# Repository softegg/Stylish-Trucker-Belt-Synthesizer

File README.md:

# Stylish-Trucker-Belt-Synthesizer
A stylus-based music synthesizer you can wear as a belt! 

Conceived as a piece of premium swag for the MAGwest convention, "Stylish!" investigates how cheaply one can make a real, useful monophonic, digital (virtual analog) music synthesizer! Borrowing the stylus-based keyboard from the venerable Stylophone, and adding complete synthesis features like multiple oscillators, filters, envelopes, vibrato, etc. that are fully adjustable so that you can make your own sounds! It may even end up with a step sequencer and drum loop! 
Let's bring real music synthesis to the masses, stylishly!

Project is based around the "Blue Pill" STM32F103C8T6 microcontroller board that can be obtained from AliExpress for less than $2.

Code is written using Arduino IDE and STM32Duino.

Audio output is via PWM (10k resistor + 1uF capacitor) using the Mozzi library. CC4.0 Share Alike Non-commercial license applies.

LEDs are WS2812B, and the project PCB includes a header to use a standard 16 LED ring.

Amplifier is XH-M125 based on the XPT8871, which you an also buy cheaply from AliExpress. Headers are included to simply mount this board on the unit if you don't want to solder all of those parts.

Speaker is 40-50mm 0.5W 8 Ohm

<br />This work is licensed under a <a rel="license" href="http://creativecommons.org/licenses/by-nc-sa/4.0/">Creative Commons Attribution-NonCommercial-ShareAlike 4.0 International License</a>.

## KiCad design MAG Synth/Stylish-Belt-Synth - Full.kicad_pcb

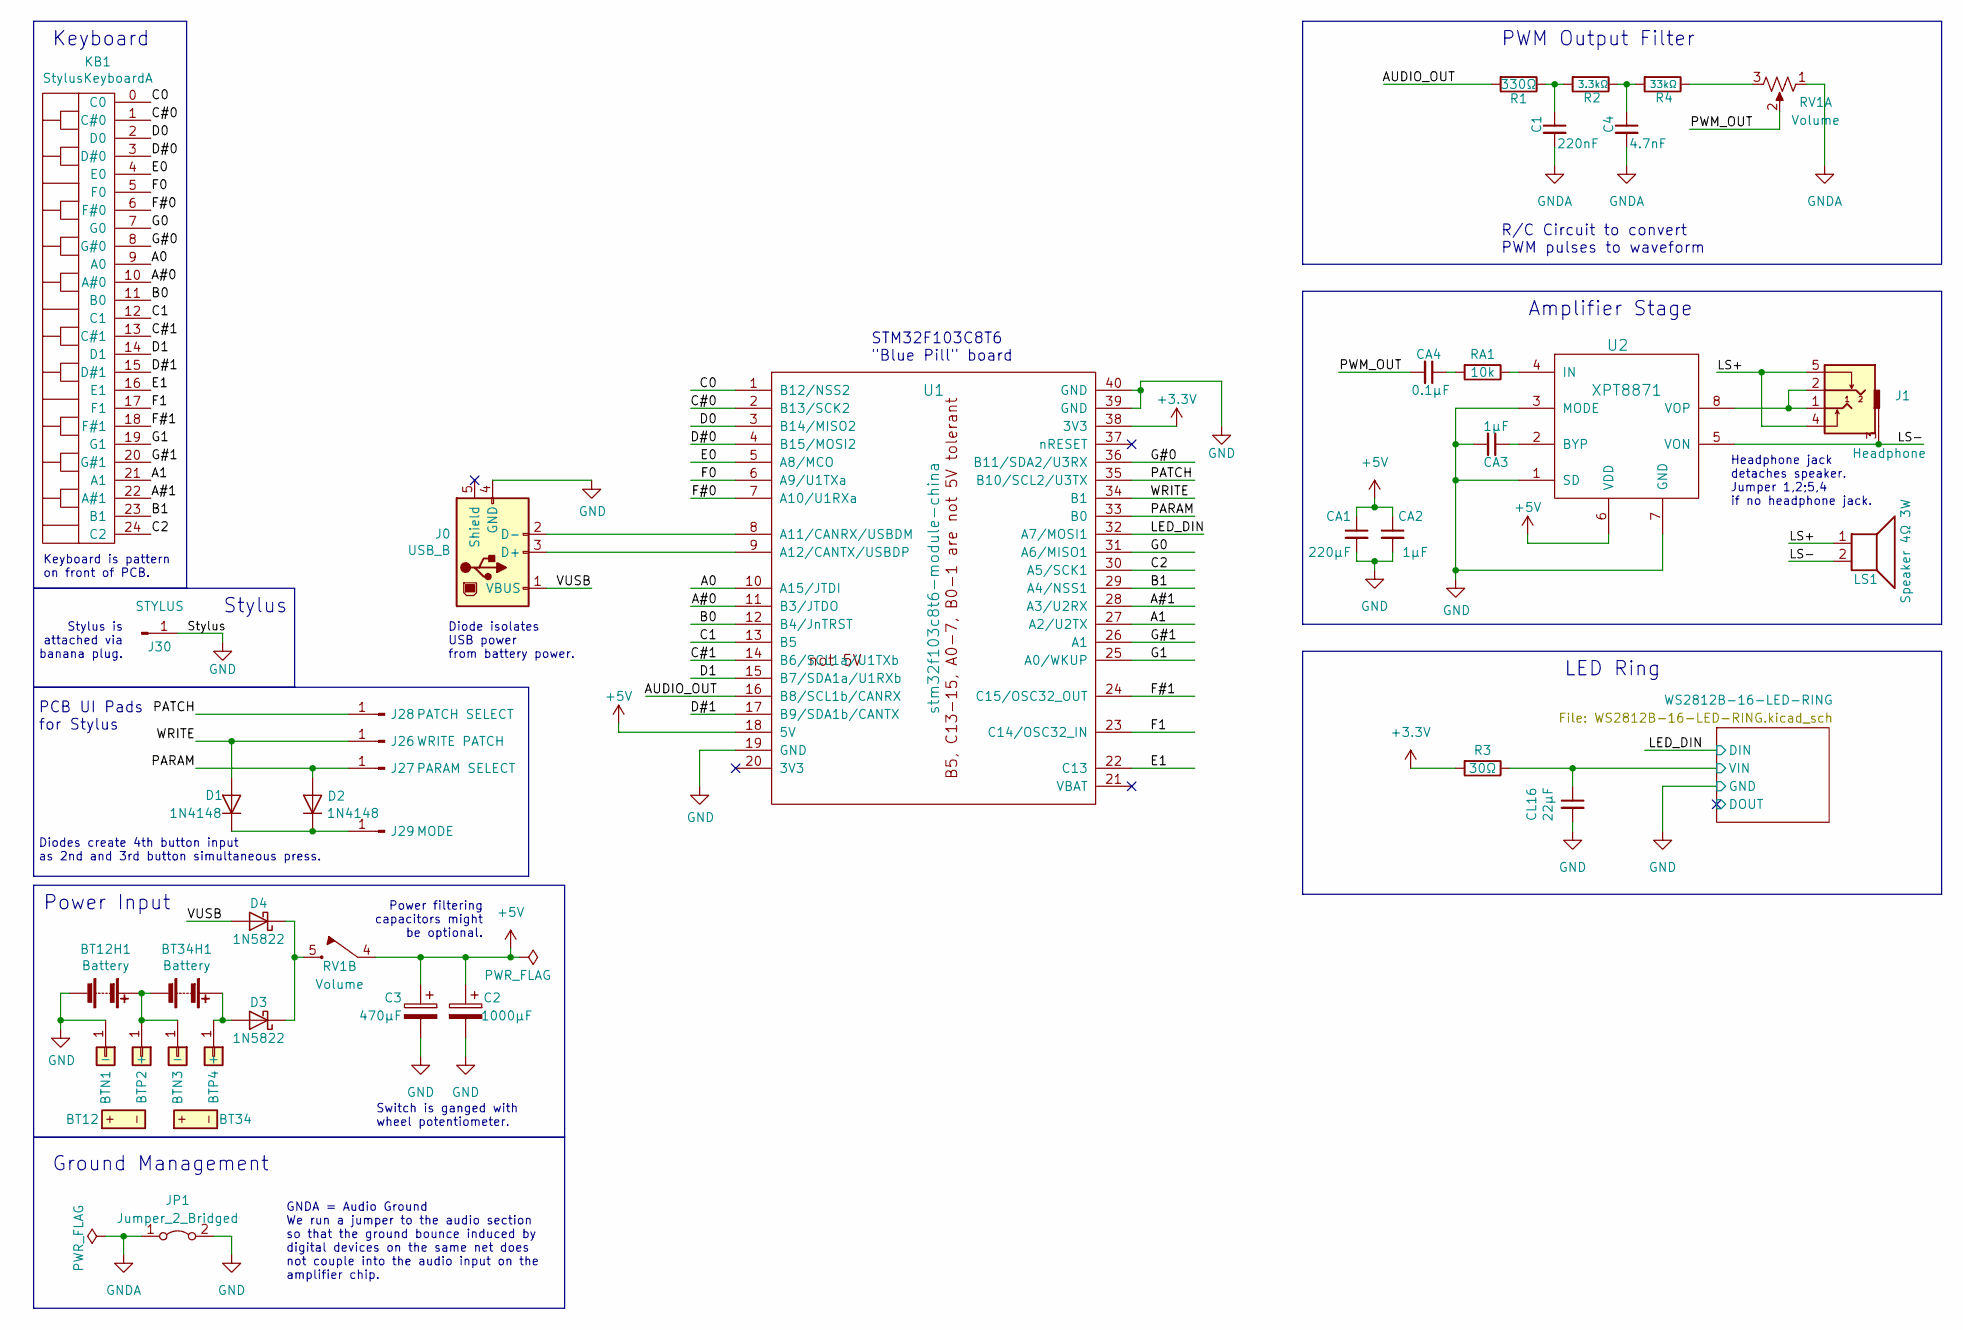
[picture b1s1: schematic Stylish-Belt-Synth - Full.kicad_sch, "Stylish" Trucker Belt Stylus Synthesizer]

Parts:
BT12, BT34: AA_Battery_Dual_Terminal
BT12H1, BT34H1: Battery; BatteryHolder_Keystone_2462_2xAA_MOD
BTN1, BTN3: -; AA_Battery_-_Terminal
BTP2, BTP4: +; AA_Battery_+_Terminal
C1: 220nF; C_Disc_D5.0mm_W2.5mm_P5.00mm+SMD
C2: 1000μF; CP_Radial_D10.0mm_P5.00mm
C3: 470μF; CP_Radial_D10.0mm_P5.00mm
C4: 4.7nF; C_Disc_D5.0mm_W2.5mm_P5.00mm+SMD
CA1: 220µF; CP_Radial_Tantal_D4.5mm_P2.50mm
CA2: 1μF; C_Disc_D5.0mm_W2.5mm_P5.00mm+SMD
CA3: 1μF; C_0805_HandSoldering
CA4: 0.1μF; C_Disc_D5.0mm_W2.5mm_P5.00mm+SMD
CL16: 22µF; C_Disc_D5.0mm_W2.5mm_P5.00mm+SMD
D1, D2: 1N4148; D_DO-35_SOD27_P7.62mm_Horizontal+SMD
D3, D4: 1N5822; D_DO-35_SOD27_P7.62mm_Horizontal+SMD
J0: USB_B
J1: Headphone; Stereo_Jack_3.5mm_Switch_Ledino_KB3SPRS
J26: WRITE PATCH; LargeRoundTouchPad
J27: PARAM SELECT; LargeRoundTouchPad
J28: PATCH SELECT; LargeRoundTouchPad
J29: MODE; LargeRoundTouchPad
J30: STYLUS; LargeRoundTouchPad
JP1: Jumper_2_Bridged
KB1: StylusKeyboardA; MAGWestSynthContactKeybed
LS1: Speaker 4Ω 3W; Pin_Header_Straight_1x02_Pitch2.54mm
R1: 330Ω; R_Axial_DIN0204_L3.6mm_D1.6mm_P7.62mm_Horizontal+SMD804
R2: 3.3kΩ; R_Axial_DIN0204_L3.6mm_D1.6mm_P7.62mm_Horizontal+SMD804
R3: 30Ω; R_Axial_DIN0204_L3.6mm_D1.6mm_P7.62mm_Horizontal+SMD804
R4: 33kΩ; R_Axial_DIN0204_L3.6mm_D1.6mm_P5mm_Horizontal+SMD804
RA1: 10k; R_Axial_DIN0204_L3.6mm_D1.6mm_P7.62mm_Horizontal+SMD804
RV1: Volume; Wheel_Pot_W_Switch_RV12_B103_FUSTAR
U1: stm32f103c8t6-module-china; stm32f103c8t6-module-china-smd
U2: XPT8871; SOIC-8-N-TP

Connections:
+3.3V: R3.2, U1.38 (3V3)
+5V: C2.1, C3.1, CA1.1, CA2.1, RV1.4, U1.18 (5V), U2.6 (VDD)
/A0: KB1.9 (A0), U1.10 (A15/JTDI)
/A1: KB1.21 (A1), U1.27 (A2/U2TX)
/A#0: KB1.10 (A#0), U1.11 (B3/JTDO)
/A#1: KB1.22 (A#1), U1.28 (A3/U2RX)
/AUDIO_OUT: R1.2, U1.16 (B8/SCL1b/CANRX)
/B0: KB1.11 (B0), U1.12 (B4/JnTRST)
/B1: KB1.23 (B1), U1.29 (A4/NSS1)
/C0: KB1.0 (C0), U1.1 (B12/NSS2)
/C1: KB1.12 (C1), U1.13 (B5)
/C2: KB1.24 (C2), U1.30 (A5/SCK1)
/C#0: KB1.1 (C#0), U1.2 (B13/SCK2)
/C#1: KB1.13 (C#1), U1.14 (B6/SCL1a/U1TXb)
/D0: KB1.2 (D0), U1.3 (B14/MISO2)
/D1: KB1.14 (D1), U1.15 (B7/SDA1a/U1RXb)
/D#0: KB1.3 (D#0), U1.4 (B15/MOSI2)
/D#1: KB1.15 (D#1), U1.17 (B9/SDA1b/CANTX)
/E0: KB1.4 (E0), U1.5 (A8/MCO)
/E1: KB1.16 (E1), U1.22 (C13)
/F0: KB1.5 (F0), U1.6 (A9/U1TXa)
/F1: KB1.17 (F1), U1.23 (C14/OSC32_IN)
/F#0: KB1.6 (F#0), U1.7 (A10/U1RXa)
/F#1: KB1.18 (F#1), U1.24 (C15/OSC32_OUT)
/G0: KB1.7 (G0), U1.31 (A6/MISO1)
/G1: KB1.19 (G1), U1.25 (A0/WKUP)
/G#0: KB1.8 (G#0), U1.36 (B11/SDA2/U3RX)
/G#1: KB1.20 (G#1), U1.26 (A1)
/LED_DIN: U1.32 (A7/MOSI1); also elsewhere on the board
/LS+: J1.4, J1.5, LS1.1
/LS-: J1.3, LS1.2, U2.5 (VON)
/PARAM: D2.2 (A), J27.1, U1.33 (B0)
/PATCH: J28.1, U1.35 (B10/SCL2/U3TX)
/PWM_OUT: CA4.2, RV1.2
/VUSB: D4.2 (A), J0.1 (VBUS)
/WRITE: D1.2 (A), J26.1, U1.34 (B1)
/WS2812B-16-LED-RING/VIN: CL16.1, R3.1; also elsewhere on the board
GND: BT12H1.2 (-), BTN1.1, C2.2, C3.2, CA1.2, CA2.2, CA3.2, CL16.2, J0.4 (GND), J30.1, JP1.2 (B), U1.19 (GND), U1.39 (GND), U1.40 (GND), U2.1 (SD), U2.3 (MODE), U2.7 (GND); also elsewhere on the board
GNDA: C1.2, C4.2, JP1.1 (A), RV1.1
unnamed: BT12H1.1 (+), BT34H1.2 (-), BTN3.1, BTP2.1
unnamed: BT34H1.1 (+), BTP4.1, D3.2 (A)
unnamed: C1.1, R1.1, R2.2
unnamed: C4.1, R2.1, R4.2
unnamed: CA4.1, RA1.2
unnamed: D1.1 (K), D2.1 (K), J29.1
unnamed: D3.1 (K), D4.1 (K), RV1.5
unnamed: J0.3 (D+), U1.9 (A12/CANTX/USBDP)
unnamed: J0.2 (D-), U1.8 (A11/CANRX/USBDM)
unnamed: R4.1, RV1.3
unnamed: CA3.1, U2.2 (BYP)
unnamed: RA1.1, U2.4 (IN)
unnamed: J1.1, J1.2, U2.8 (VOP)

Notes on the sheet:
Stylus is attached via banana plug.
GNDA = Audio Ground We run a jumper to the audio section so that the ground bounce induced by digital devices on the same net does not couple into the audio input on the amplifier chip.
Power filtering capacitors might be optional.
Amplifier Stage
PCB UI Pads for Stylus
Stylus
Diode isolates USB power from battery power.
Keyboard
Headphone jack detaches speaker. Jumper 1,2;5,4 if no headphone jack.
Switch is ganged with wheel potentiometer.
Diodes create 4th button input as 2nd and 3rd button simultaneous press.
Ground Management
LED Ring
R/C Circuit to convert PWM pulses to waveform
Keyboard is pattern on front of PCB.
PWM Output Filter
STM32F103C8T6 "Blue Pill" board
Power Input

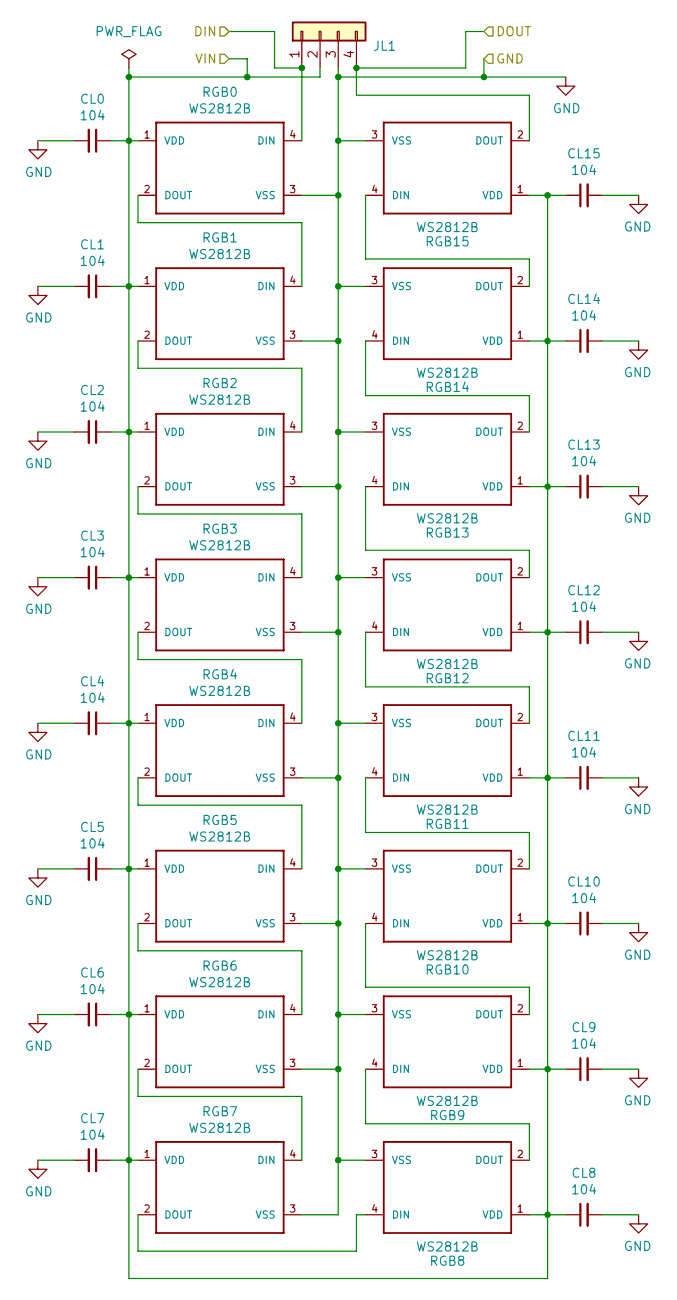
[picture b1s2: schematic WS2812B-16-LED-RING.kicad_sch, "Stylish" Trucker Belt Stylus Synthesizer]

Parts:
CL0, CL1, CL2, CL3, CL4, CL5, CL6, CL7, CL8, CL9, CL10, CL11, CL12, CL13, CL14, CL15: 104; C_0805_HandSoldering
JL1: Pin_Header_Straight_1x04_Pitch2.54mm
RGB0, RGB1, RGB2, RGB3, RGB4, RGB5, RGB6, RGB7, RGB8, RGB9, RGB10, RGB11, RGB12, RGB13, RGB14, RGB15: WS2812B

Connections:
/LED_DIN: JL1.1, RGB0.4 (DIN); also elsewhere on the board
/WS2812B-16-LED-RING/DOUT: JL1.4, RGB15.2 (DOUT)
/WS2812B-16-LED-RING/VIN: CL0.1, CL1.1, CL2.1, CL3.1, CL4.1, CL5.1, CL6.1, CL7.1, CL8.1, CL9.1, CL10.1, CL11.1, CL12.1, CL13.1, CL14.1, CL15.1, JL1.2, RGB0.1 (VDD), RGB1.1 (VDD), RGB2.1 (VDD), RGB3.1 (VDD), RGB4.1 (VDD), RGB5.1 (VDD), RGB6.1 (VDD), RGB7.1 (VDD), RGB8.1 (VDD), RGB9.1 (VDD), RGB10.1 (VDD), RGB11.1 (VDD), RGB12.1 (VDD), RGB13.1 (VDD), RGB14.1 (VDD), RGB15.1 (VDD); also elsewhere on the board
GND: CL0.2, CL1.2, CL2.2, CL3.2, CL4.2, CL5.2, CL6.2, CL7.2, CL8.2, CL9.2, CL10.2, CL11.2, CL12.2, CL13.2, CL14.2, CL15.2, JL1.3, RGB0.3 (VSS), RGB1.3 (VSS), RGB2.3 (VSS), RGB3.3 (VSS), RGB4.3 (VSS), RGB5.3 (VSS), RGB6.3 (VSS), RGB7.3 (VSS), RGB8.3 (VSS), RGB9.3 (VSS), RGB10.3 (VSS), RGB11.3 (VSS), RGB12.3 (VSS), RGB13.3 (VSS), RGB14.3 (VSS), RGB15.3 (VSS); also elsewhere on the board
unnamed: RGB0.2 (DOUT), RGB1.4 (DIN)
unnamed: RGB1.2 (DOUT), RGB2.4 (DIN)
unnamed: RGB2.2 (DOUT), RGB3.4 (DIN)
unnamed: RGB3.2 (DOUT), RGB4.4 (DIN)
unnamed: RGB4.2 (DOUT), RGB5.4 (DIN)
unnamed: RGB5.2 (DOUT), RGB6.4 (DIN)
unnamed: RGB6.2 (DOUT), RGB7.4 (DIN)
unnamed: RGB7.2 (DOUT), RGB8.4 (DIN)
unnamed: RGB8.2 (DOUT), RGB9.4 (DIN)
unnamed: RGB9.2 (DOUT), RGB10.4 (DIN)
unnamed: RGB10.2 (DOUT), RGB11.4 (DIN)
unnamed: RGB11.2 (DOUT), RGB12.4 (DIN)
unnamed: RGB12.2 (DOUT), RGB13.4 (DIN)
unnamed: RGB13.2 (DOUT), RGB14.4 (DIN)
unnamed: RGB14.2 (DOUT), RGB15.4 (DIN)

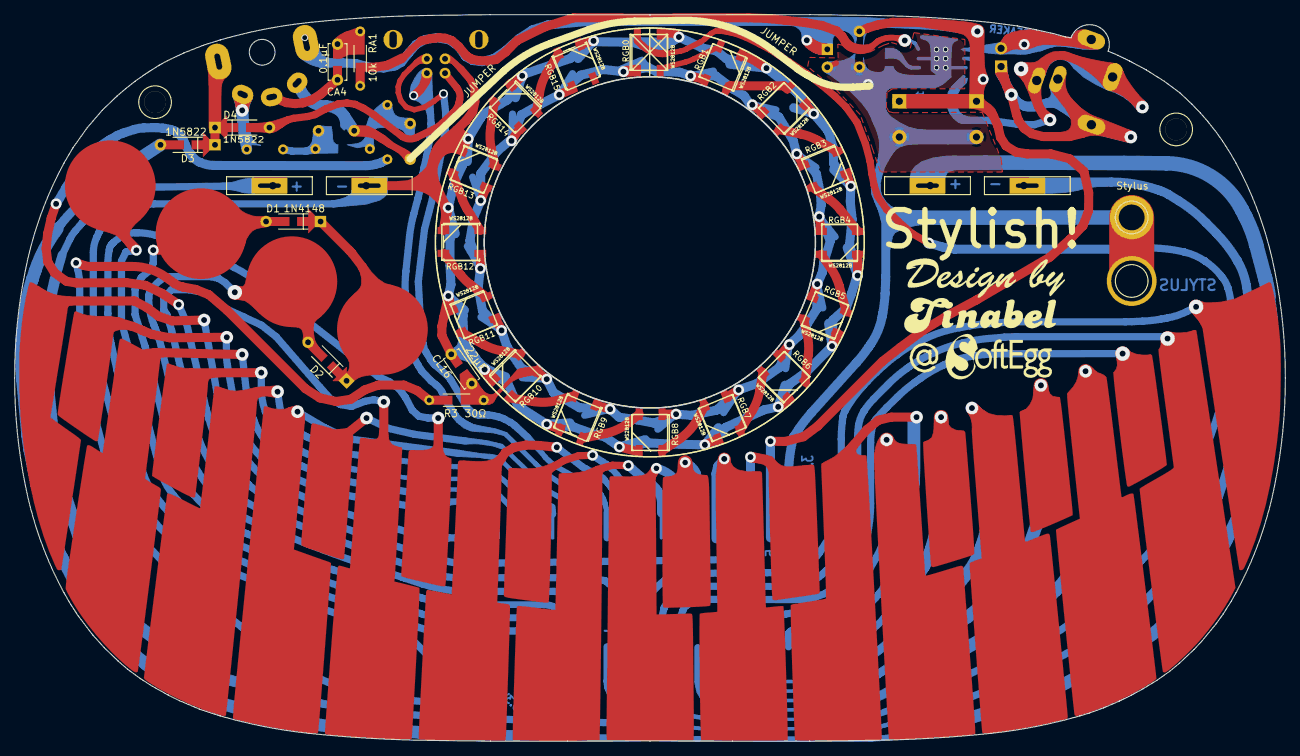
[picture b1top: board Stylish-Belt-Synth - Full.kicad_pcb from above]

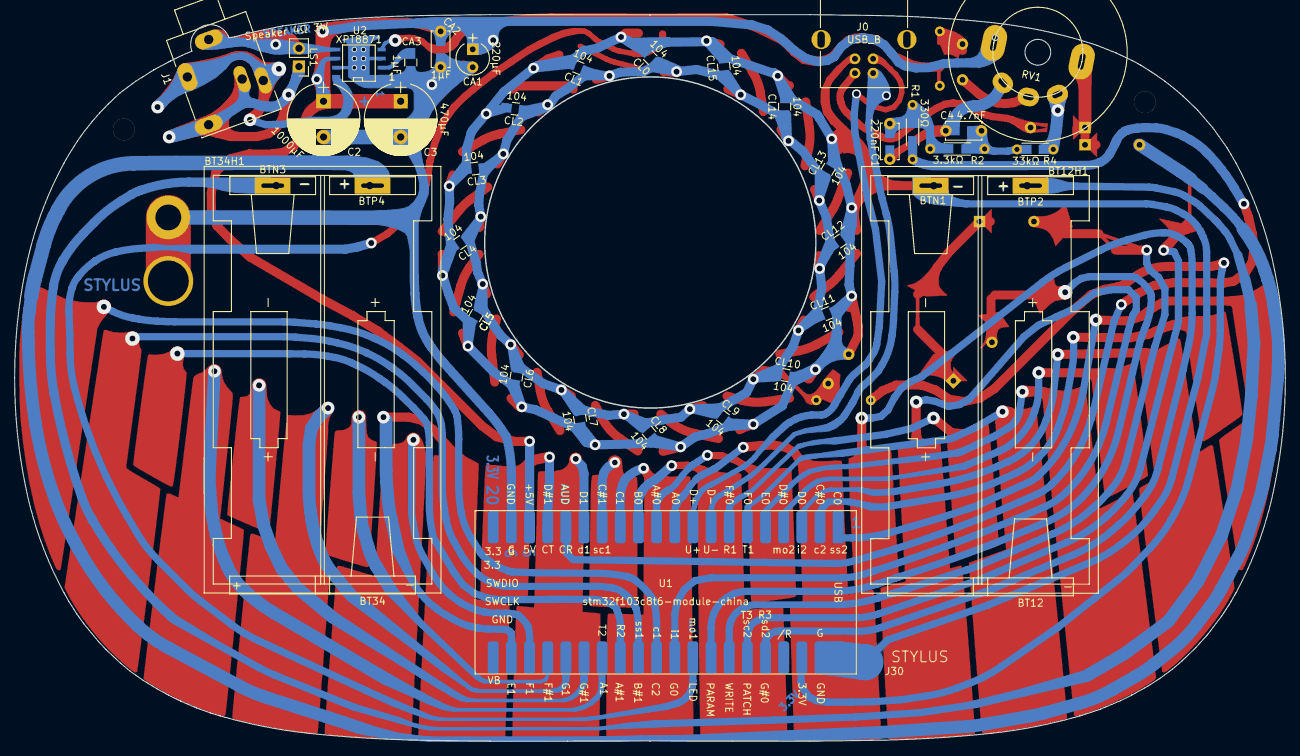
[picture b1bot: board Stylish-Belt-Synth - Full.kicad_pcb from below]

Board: 2 copper layers, 177.7 x 101.6 mm, 71 parts (41 on the bottom side), 67 nets.

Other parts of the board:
Stylus: Stylus; 1pin

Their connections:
GND: Stylus.1; also elsewhere on the board

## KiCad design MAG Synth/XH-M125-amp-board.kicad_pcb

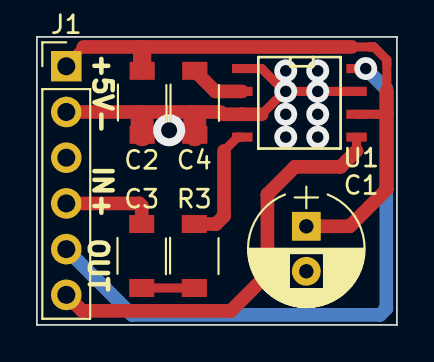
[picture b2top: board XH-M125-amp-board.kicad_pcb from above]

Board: 2 copper layers, 20.0 x 16.0 mm, 7 parts (0 on the bottom side), 8 nets.

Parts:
C1: 470uF; CP_Radial_D6.3mm_P2.50mm
C2, C4: 1uF; C_1509
C3: 0.39uF; C_1509
J1: Conn_01x06; Pin_Header_Straight_1x06_Pitch2.54mm
R3: R; C_1509
U1: XPT8871; SOIC-8-N

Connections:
/GND: C1.2, C2.2, C4.2, J1.2, J1.3, U1.1, U1.3, U1.7
/VCC: C1.1, C2.1, J1.1, U1.6
/VIN: C3.2, J1.4
/VO1: J1.6, U1.5
/VO2: J1.5, U1.8
unnamed: C3.1, R3.2
unnamed: C4.1, U1.2
unnamed: R3.1, U1.4

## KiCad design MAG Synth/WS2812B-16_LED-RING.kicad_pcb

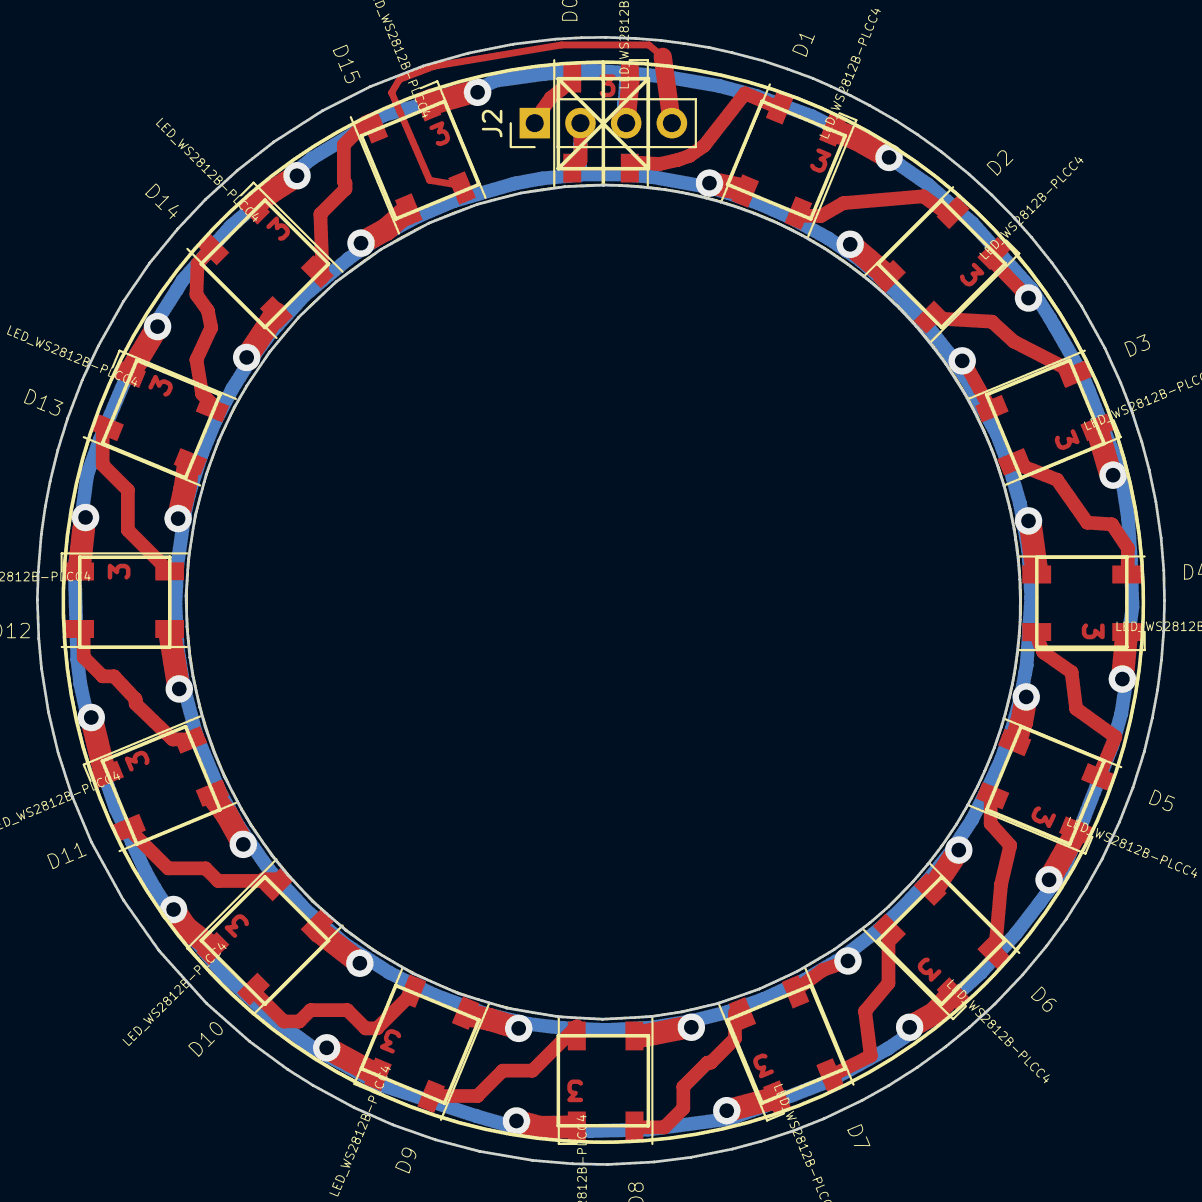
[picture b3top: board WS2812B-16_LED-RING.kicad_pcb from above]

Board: 2 copper layers, 62.6 x 62.6 mm, 17 parts (0 on the bottom side), 19 nets.

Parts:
D0, D1, D2, D3, D4, D5, D6, D7, D8, D9, D10, D11, D12, D13, D14, D15: LED_WS2812B-PLCC4
J2: Pin_Header_Straight_1x04_Pitch2.54mm

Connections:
/WS2812B-16-LED-RING/5V: D0.1, D1.1, D2.1, D3.1, D4.1, D5.1, D6.1, D7.1, D8.1, D9.1, D10.1, D11.1, D12.1, D13.1, D14.1, D15.1, J2.2
/WS2812B-16-LED-RING/DIN: D0.4, J2.1
/WS2812B-16-LED-RING/DOUT: D15.2, J2.4
/WS2812B-16-LED-RING/GND: D0.3, D1.3, D2.3, D3.3, D4.3, D5.3, D6.3, D7.3, D8.3, D9.3, D10.3, D11.3, D12.3, D13.3, D14.3, D15.3, J2.3
unnamed: D0.2, D1.4
unnamed: D1.2, D2.4
unnamed: D2.2, D3.4
unnamed: D3.2, D4.4
unnamed: D4.2, D5.4
unnamed: D5.2, D6.4
unnamed: D6.2, D7.4
unnamed: D7.2, D8.4
unnamed: D8.2, D9.4
unnamed: D10.2, D11.4
unnamed: D9.2, D10.4
unnamed: D11.2, D12.4
unnamed: D12.2, D13.4
unnamed: D13.2, D14.4
unnamed: D14.2, D15.4

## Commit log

2018-10-01 First Commit! Includes relevant PCB files and source files. WS2812B_test and stylus_keypad_test work. Pot_test was for prototyping board with pots and it worked too. Stylish.pde used to work and no l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
2018-10-01 Test commit to make sure git works.
2018-10-01 Keyboard with debouncing routines and key up and key down callback functions. Note that distinction between buttons and keys has been eliminated; that should happen outside of the keyboard loop. Not 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
2018-10-04 Code now lets you play music!
2018-10-07 1st draft of case. Updates to PCB for battery holder mounting and other stuff. Gerbers added for Tindie. Updates to source code, although I don't know if they are the in progress state machine update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
2018-10-11 Schematic updated with USB and diodes for MODE button. Source code updated with state machine in process.
2018-10-17 New power switch. 3d model included. 3d model of the amp board included. PCB redesign in progress.
2018-10-17 Updated footprints. Including STL for speaker holder.
2018-10-17 V0.2 PCB completed! Schematic, PCB, and Gerbers updated.
2018-10-23 PCB tweaked a little. Zig zag cut line generated on User 1 layer. Souce code: state machine in progress.
2018-11-03 More work on state machine source. 3d models for 3d printing added
2018-12-11 Latest
2018-12-11 Full with protel extentions
2019-03-18 Updated PCB to have contiguous outline. Yet another incomplete reworking of the state machine.
2019-03-18 Adding 3d models as exported from KiCAD and the textures to put on them
2019-06-09 V3 board V2.4 case
2019-06-11 Moving around the gerbers
2019-06-15 Updated PCB and V2 Enclosure back
2019-06-25 More board cleanup. Fixed values of parts based on test board construction. Rewired potentiometer so that low volume is nearest the power on/off click. More hand vias where they are needed.
2019-07-08 PCB V4 update Wood CNC models added
2019-07-08 Top Fixture
2019-07-11 Small updates to PCB. One footprint changed so all SMD are 0805. BOM added. V1 of Source Code added.
2019-07-11 V4.1 PCB Gerbers return.
2019-07-11 Final Renders of PCB
2019-07-12 Step files for V2 and V4 for Bruce
2019-07-13 Updated PCB to have heat dissipation for the amplifier chip. Risky last minute changes...
2019-07-13 Changed LED ring resistor from 44Ω to 30Ω.
2019-07-13 Updated BOM with new speaker, and lower value LED ring resistor.
2019-07-13 Delete Stylish-Belt-Synth - Full-Edge_Cuts.gbr
    Went to protel extensions
2019-07-13 Delete Stylish-Belt-Synth - Full-F_Cu.gbr
    Went to protel extensions
2019-07-13 Delete Stylish-Belt-Synth - Full-B_Cu.gbr
    went to protel extensions
2019-07-13 Added photos showing assembly detail.
2019-07-14 Moved silkscreen for U2 to not be under the chip where we need connection to the ground plane. Updated Gerbers to match. Updated 3d renders for texture map.
2019-07-14 Update PCB 3d model.
2019-07-16 3d models for wood CNC
2019-07-16 Wood CNC Aspire files for top
2019-07-17 Photos of thin traces
2019-07-18 Completion of wood CNC paths for Aspire.
2019-07-19 85% complete new V4 plastic enclosure
2019-07-19 Added inner plastic lip to plastic V4 model. Finished PCB supports. PCB now screws into the top. TODO: Add screw holes to the edges, Battery compartments.
2019-07-30 Wood CNC integrated into one file, updated to 8.5 to get around bug. LED code updated to show white first as the best test for LEDs. Keyboard code updated to test buttons correctly.
2019-07-30 Moved Speaker down 2mm
2019-07-30 Allowance for the tip of the stylus connector in Wood CNC and other fun things.
2019-07-31 3d models updated to proper clearances. Aspire files in progress.
2019-08-01 Updated wood models and aspire for top.
2019-08-04 Update all Wood CNC models, Aspire, and gcode
2019-08-07 Model updates for fixed lightpipe cutout. Aspire update for fixed lightpipe cutout. Gcode update for 1 inch top wood thickness.
2019-08-12 Updated Fixtures. Volume wheel model for 3d print
2019-08-14 Updating for SHARK CNC
2019-08-29 Shark CNC aspire and gcode files for wood CNC. Work on synth source code.
2019-09-03 Updated Shark CNC Aspire and g-code files. Batch file for combining the g-code added. Work on the real synth source code: bit packing for patch storage complete. button detection fixed.
2019-09-07 Source code update: UI working!
2019-09-09 Noise and Envelope. Some default sound data. Write and restore patches kinda works.
2019-09-10 Filter added and attached to envelope. Stat on LFO. Fiked patch bookkeeping... still needs flash write.
2019-09-11 All synth parameters implemented except PWM and env to noise (which might be useless). Patches now save correctly to Flash!
2019-09-12 Before I add brightness.
2019-09-12 Brightness is parameter 0 on mode bits
2019-09-13 Quick Manual!
2019-10-15 Finally! The plastic case V4 for the "final" PCB! Works with the volume control and all jacks! Haven't tested it yet!
2019-10-15 STEP files of "final" plastic case for V4 PCB.
2019-10-18 Fixed tuning in source code. Allow for patch reset by holding down patch select button on power on. Mode parameters: LED bright (C0) Coarse Pitch (C#0) Fine Pitch (D0) Updates to battery door models 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
2019-10-28 Removed old files for plastic enclosure
2019-11-03 Trimmed tabs on the battery doors for a better fit. Hopefullt I didn't make them too small.
2019-11-05 Added protomold quotes PDF
2019-12-03 Noted value of speaker in Schematic
2019-12-06 Updated manual: Added tuning options. Added page numbers. Added schematic.
2019-12-30 Top Inner Mold Mold
2020-01-27 Mold Molds and Negatives
2020-01-29 Battery Door Mold Molds
2020-02-13 Top Negatives, walls for battery door molds, thin battery doors
2020-03-12 Moved and renamed files to new directory structure, this time using "git mv". Added in the models for LED Bezels and Lightpipes.
2020-03-12 Cleaned up directories even more!
2020-03-12 Fixed some names for consistency.
2020-03-12 Fix windows non-case sensitivity / GIT *UX case sensitivity error in OLD / old directory.
2020-03-12 Put updated README.md back.
2020-03-14 Hollow versions of mold molds for SLA printing. LED Lightpipe Outside Positive.
2020-03-19 Adding hollow STL parts for mold molds to conserve material. Also mold walls for LED bezel. Saved a STEP version of the LED Bezel, because my Fusion startup license expired and they haven't renewed i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
2020-05-11 Updated hollow mold molds to be thicker / more printable (maybe?). Updated Shark CNC gcode to put the jumper slot back in. Added binary files of built source code for direct uploading.
2023-05-01 Updated files to latest KiCad Added PDF and SVG versions of schematics Added PDF for PCB front and back reference Added photos of completed units and pcbs
2023-11-15 Added cache.lib, hopefully that solves missing footprints.
2023-11-15 Inside positive step file added
2023-11-16 Oh, you wanted this one.
2023-11-22 Fixes for removing LED noise from the audio. Thanks Brandon for the hard work in figuring this out!
2023-11-24 Updated fix for audio problems, adds AGND to C4 too. 3d models for parts extracted from old PCB model - only partly complete
2023-11-24 Schematic update
    All ERC errors resolved. 100+ ERC warnings remain.
2023-11-25 Corrected orientation of components to match the PCB again
2023-11-25 PCB now probably matches schematic. 3d parts now mostly centered 3d parts all updated and should appear properly if not, make sure to adjust the directories for your system, because I don't know how 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
2023-12-11 Changed the font in the manual so that Brandon could read it. I thought the old one looked cooler and was fine, but I guess not. Nobody had ever said anything before. Well, it's changed now.
2025-10-22 Special "3d print only" parts with thickened details that might not be injection mold friendly. Update on the PCB. Blue pill 3d model Updated Volume Wheel.
